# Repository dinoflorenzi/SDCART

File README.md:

# SDCART
Interfaccia per il caricamento programmi da micro SD. Il progetto deriva dal progetto SDDRIVE di Deniel Coloumn (http://dcmoto.free.fr/bricolage/sddrive/index_v2.html) a cui spettano tutti i meriti di sviluppo hardware e software il driver ed il software di gestione. 
La variante SDCART consiste nell'utilizzo dello slot della cartuccia invece che lo slot di espanzione e l'utilizzo di memorie eeprom AT28C64/256 che danno la possibilità di aggiornare il software direttamente da PC128.</br>
</br>
La micro SD può essere formattata FAT o FAT32 utilizzando il massimo spazio di allocazione. Il limite di capacità è di 32 GByte. Dopo la formattazione deve essere copiato SDDRIVE.SEL come primo file. Successivamente si possono copiare le immagini dei floppy con estensione .SD. Ogni files .SD contiene l'immagine di due floppy virtuali da 360Kb, accessibili da BASIC come device da 0 a 3.
Il file immagine è selezionabile tramite un programma SDDRIVE.SEL che elenca il contenuto della micro SD, e che si avvia alla selezione del BASIC128 o BASIC1.0 del MENU principale del PC128.</br>
***** ATTENZIONE TUTTI I FILE DEVONO ESSERE CONTENUTI NELLA ROOT *****</br>
Per cambiare file immagine provare con RESET ma spesso è necessario spegnere il riaccendere il PC128.</br>.

</br>
E' possibile inoltre caricare i files .SDDRIVE generati dalla funzione SNAPSHOT dell'emulatore DCMOTO, che permette il salvataggio e ripristino della situazione del PC128.

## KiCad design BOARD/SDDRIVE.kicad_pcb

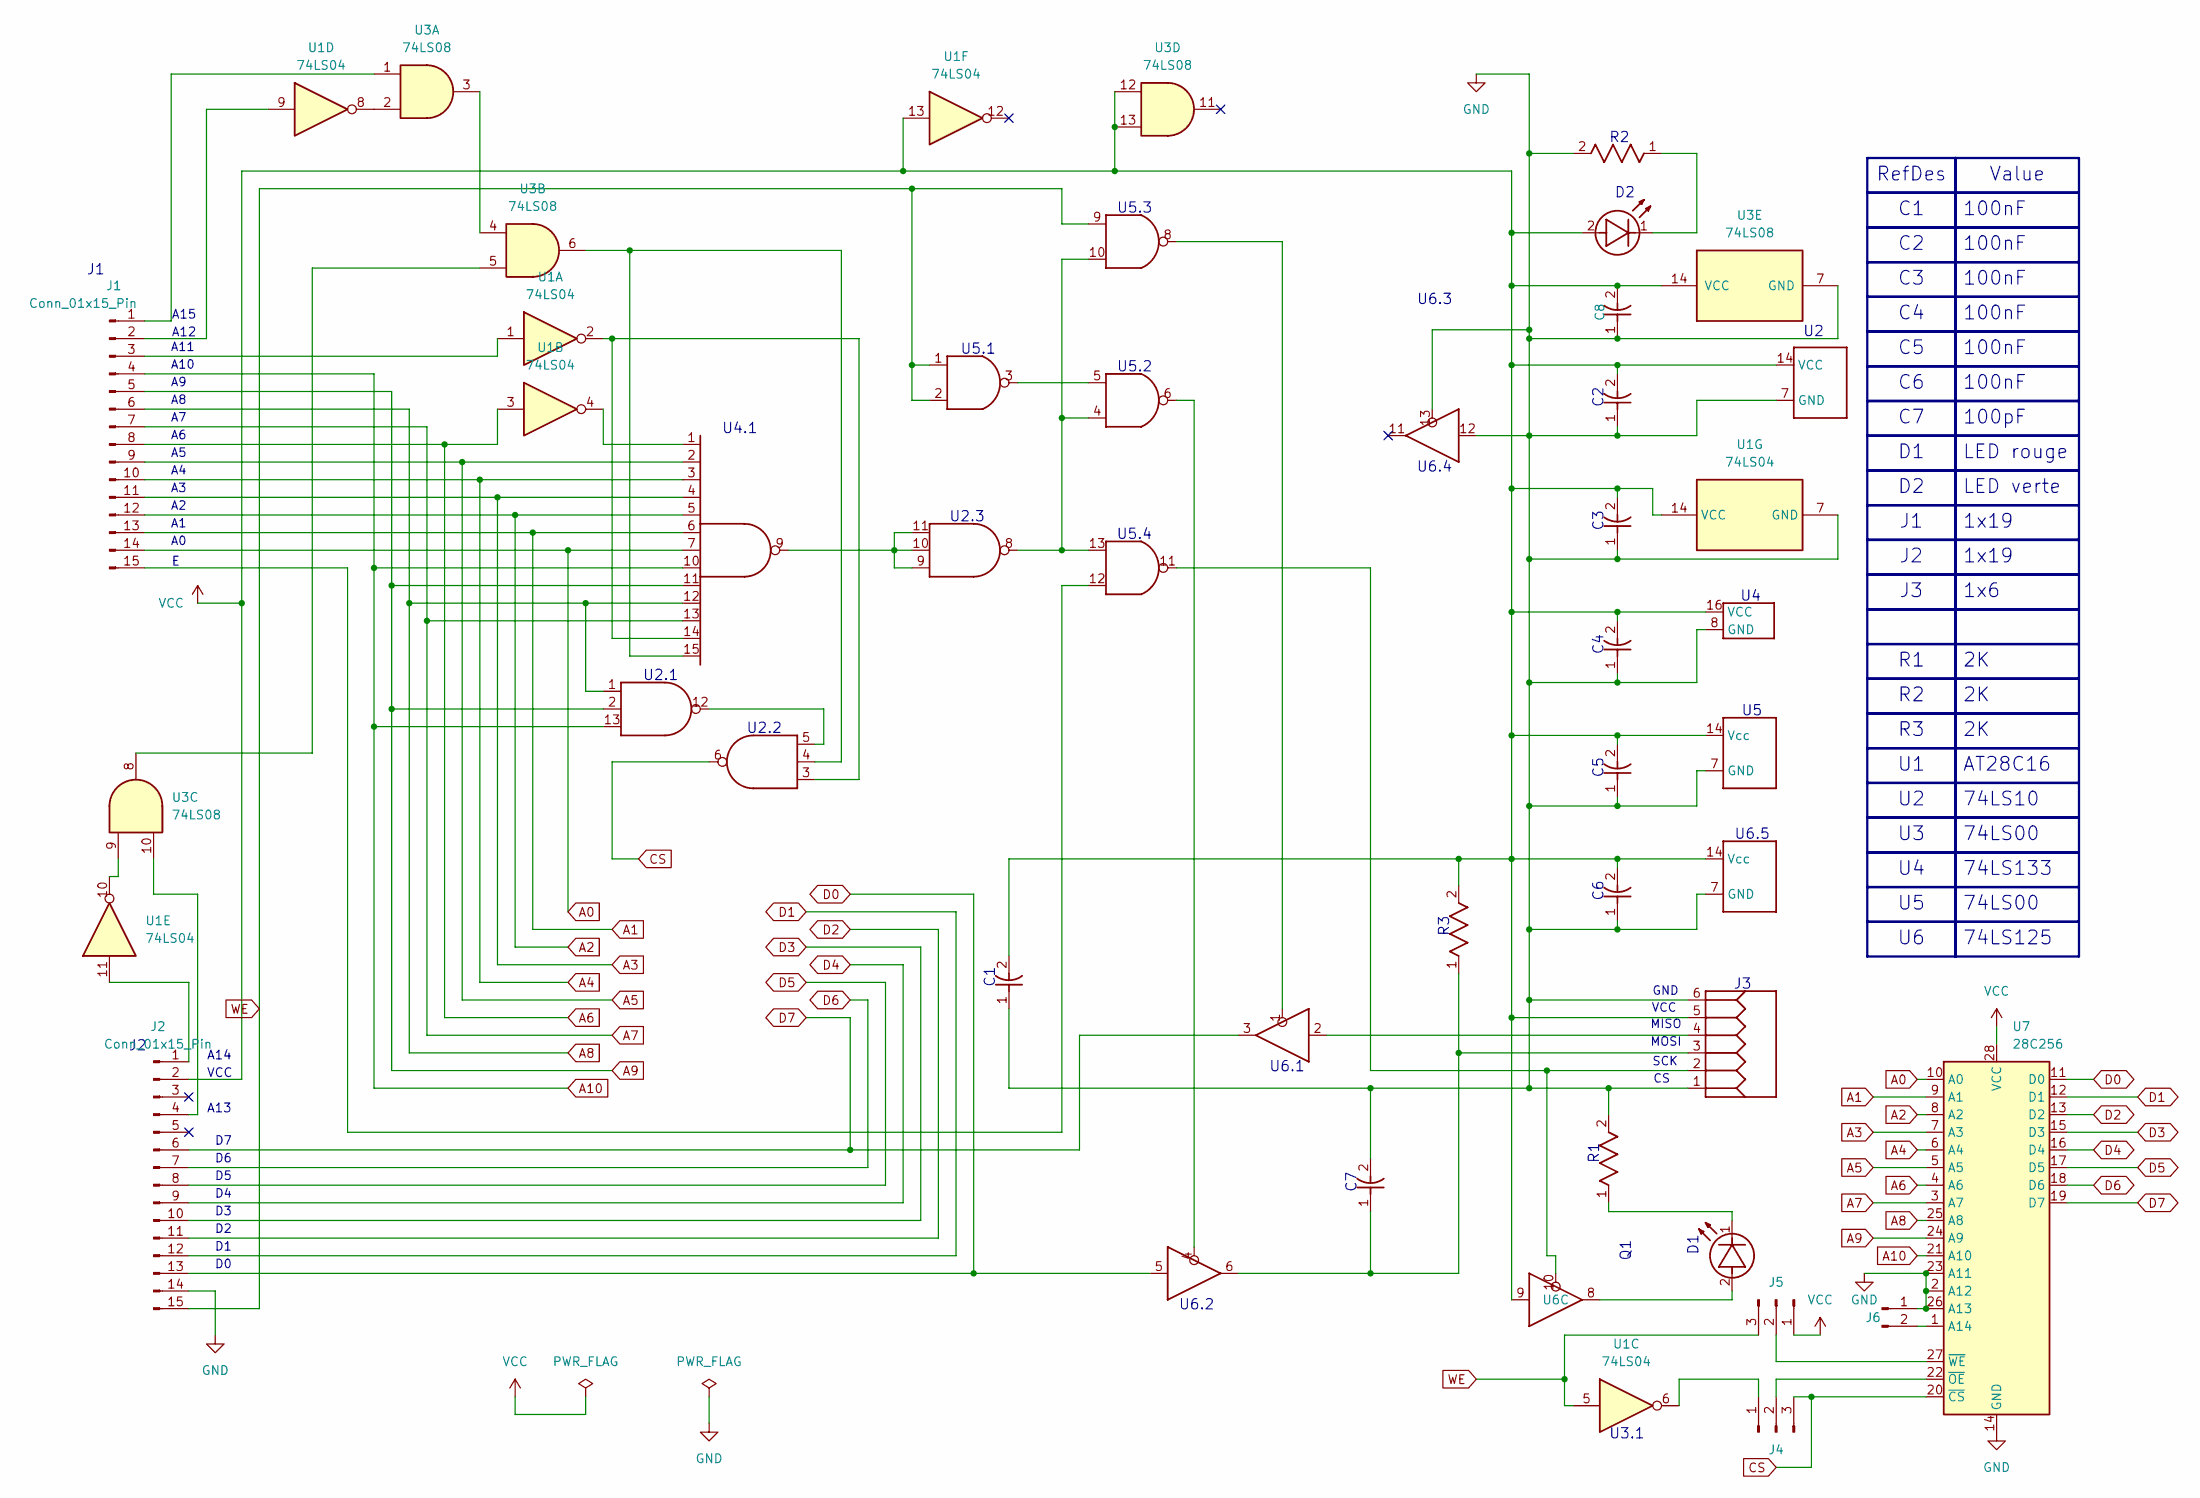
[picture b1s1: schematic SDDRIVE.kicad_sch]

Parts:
C1, C2, C3, C4, C5, C7, C8: CAP200; C_Disc_D4.7mm_W2.5mm_P5.00mm
C6: CAP200_1; C_Disc_D4.7mm_W2.5mm_P5.00mm
D1: LED; LED_D3.0mm
D2: LED_11; LED_D3.0mm
J1, J2: Conn_01x15_Pin; EdgeConn_15
J3: HDRF-1X6; PinHeader_1x06_P2.54mm_Vertical
J4, J5: Conn_01x03_Pin; PinHeader_1x03_P2.54mm_Vertical
J6: Conn_01x02_Pin; PinHeader_1x02_P2.54mm_Vertical
R1, R2, R3: RES; R_Axial_DIN0204_L3.6mm_D1.6mm_P7.62mm_Horizontal
U1: 74LS04; DIP-14_W7.62mm
U2: SN74LS10N; DIP-14_W7.62mm
U3: 74LS08; DIP-14_W7.62mm
U4: SN74ALS133N; DIP-16_W7.62mm
U5: SN74LS00N; DIP-14_W7.62mm
U6: SN74LS125N; DIP-14_W7.62mm
U7: 28C256; DIP-28_W15.24mm

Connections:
A0: J1.14, U4.7 (G), U7.10 (A0)
A1: J1.13, U4.6 (F), U7.9 (A1)
A2: J1.12, U4.5 (E), U7.8 (A2)
A3: J1.11, U4.4 (D), U7.7 (A3)
A4: J1.10, U4.3 (C), U7.6 (A4)
A5: J1.9, U4.2 (B), U7.5 (A5)
A6: J1.8, U1.3, U7.4 (A6)
A7: J1.7, U4.13 (K), U7.3 (A7)
A8: J1.6, U2.1 (A), U4.12 (J), U7.25 (A8)
A9: J1.5, U2.2 (B), U4.11 (I), U7.24 (A9)
A10: J1.4, U2.13 (C), U4.10 (H), U7.21 (A10)
CS: J4.3, U2.6 (Y), U7.20 (~CS)
D0: J2.13, U6.5 (D), U7.11 (D0)
D1: J2.12, U7.12 (D1)
D2: J2.11, U7.13 (D2)
D3: J2.10, U7.15 (D3)
D4: J2.9, U7.16 (D4)
D5: J2.8, U7.17 (D5)
D6: J2.7, U7.18 (D6)
D7: J2.6, U6.3 (O), U7.19 (D7)
GND: C1.1, C2.1, C3.1, C4.1, C5.1, C6.1, C7.2, C8.1, J2.14, J3.1, J3.6, J6.1, R1.2 (B), R2.2 (B), U1.7 (GND), U2.7 (GND), U3.7 (GND), U4.8 (GND), U5.7 (GND), U6.7 (GND), U6.12 (D), U6.13 (~E), U7.2 (A12), U7.14 (GND), U7.23 (A11), U7.26 (A13)
unnamed: D1.2 (A), U6.8 (O)
unnamed: D1.1 (K), R1.1 (A)
unnamed: D2.1 (K), R2.1 (A)
unnamed: J1.1, U3.1
unnamed: J1.2, U1.9
unnamed: J1.3, U1.1
unnamed: J1.15, U5.12
unnamed: J2.1, U1.11
unnamed: J2.4, U3.10
unnamed: J3.2, U5.11, U6.10 (~E)
unnamed: C7.1, J3.3, R3.1 (A), U6.6 (O)
unnamed: J3.4, U6.2 (D)
unnamed: J4.1, U1.6
unnamed: J4.2, U7.22 (~OE)
unnamed: J5.2, U7.27 (~WE)
unnamed: J6.2, U7.1 (A14)
unnamed: U1.8, U3.2
unnamed: U1.10, U3.9
unnamed: U2.5 (C), U2.12 (Y)
unnamed: U1.2, U2.3 (A), U4.14 (L)
unnamed: U2.4 (B), U3.6, U4.15 (M)
unnamed: U2.9 (A), U2.10 (B), U2.11 (C), U4.9 (Y)
unnamed: U2.8 (Y), U5.4, U5.10, U5.13
unnamed: U3.3, U3.4
unnamed: U3.5, U3.8
unnamed: U1.4, U4.1 (A)
unnamed: U5.3, U5.5
unnamed: U5.8, U6.1 (~E)
unnamed: U5.6, U6.4 (~E)
VCC: C1.2, C2.2, C3.2, C4.2, C5.2, C6.2, C8.2, D2.2 (A), J2.2, J3.5, J5.1, R3.2 (B), U1.13, U1.14 (VCC), U2.14 (VCC), U3.12, U3.13, U3.14 (VCC), U4.16 (VCC), U5.14 (Vcc), U6.9 (D), U6.14 (Vcc), U7.28 (VCC)
WE: J2.15, J5.3, U1.5, U5.1, U5.2, U5.9

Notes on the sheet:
SCK
LED verte
U6.1
MISO
100nF
A14
LED rouge
U6.4
A12
VCC
U6.3
U5.3
1x19
U2.2
MOSI
U6.5
74LS00
1x6
U4.1
A15
Value
100pF
U5.4
74LS133
A10
74LS10
U2.3
U5.2
RefDes
U3.1
U5.1
AT28C16
U2.1
A13
A11
74LS125
GND
U6.2

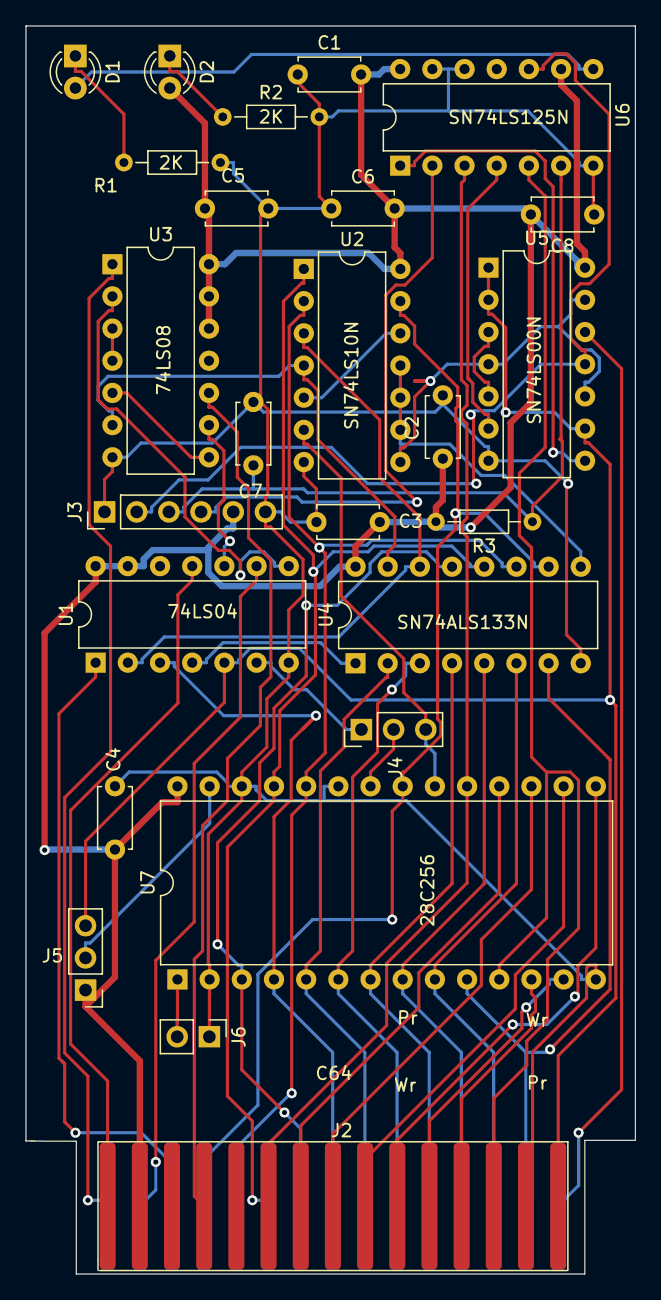
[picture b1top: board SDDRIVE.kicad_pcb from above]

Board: 2 copper layers, 48.1 x 98.5 mm, 26 parts (1 on the bottom side), 52 nets.

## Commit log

2026-01-02 Add files via upload
    Programma per la selezione dei file immagine nella MicroSD. Il file deve essere trasferito per primo nella micro sd dopo la formattazione.
2026-01-02 Update README with download links for programs
    Added download links for installable programs on micro SD.
2026-01-02 Update README with line breaks in links
2026-01-02 Update README with project details and origin
    Added project origin and details about SDCART variant.
2026-01-02 Update README with image and formatting fix
    Added image reference and fixed formatting in README.
2026-01-02 Add STL image reference to README
    Added STL file image to README for reference.
2026-01-02 Remove STL image from README
    Removed STL image reference from README.
2026-01-02 Update README with micro SD details
    Added information about micro SD formatting and usage.
2026-01-02 Replace images in README with updated visuals
    Updated images in README to reflect new visuals.
2026-01-02 Update image selection instructions in README
2026-01-02 Update README with image file change instructions
    Added instructions for changing image files and using SNAPSHOT files.
2026-01-02 Revise README for clarity on floppy images and file structure
    Updated README to clarify the number of virtual floppy images and added a note about file structure.
2026-01-02 Update README with micro SD formatting details
    Clarify micro SD formatting instructions and allocation space.
2026-01-10 Refine README.md language for better clarity
    Corrected punctuation and improved sentence structure for clarity.
